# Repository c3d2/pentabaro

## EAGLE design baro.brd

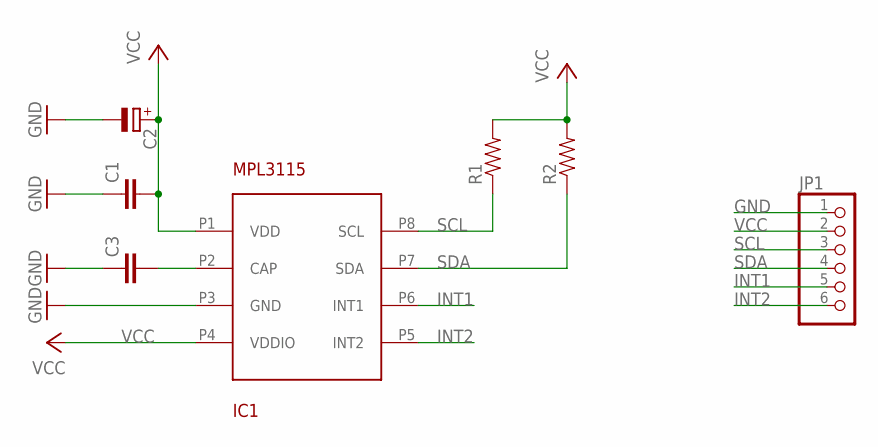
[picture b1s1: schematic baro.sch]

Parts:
C1, C3: CAP0805; 0805
C2: CPOL-EUSMCC; SMC_C
IC1: MPL3115A2; LGA8
JP1: PINHD-1X6; 1X06
R1, R2: RESISTOR0805-RES; 0805

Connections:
GND: C1.1, C2.-, C3.1, IC1.P3 (GND), JP1.1
INT1: IC1.P6 (INT1), JP1.5
INT2: IC1.P5 (INT2), JP1.6
unnamed: C3.2, IC1.P2 (CAP)
SCL: IC1.P8 (SCL), JP1.3, R1.1
SDA: IC1.P7 (SDA), JP1.4, R2.1
VCC: C1.2, C2.+, IC1.P1 (VDD), IC1.P4 (VDDIO), JP1.2, R1.2, R2.2

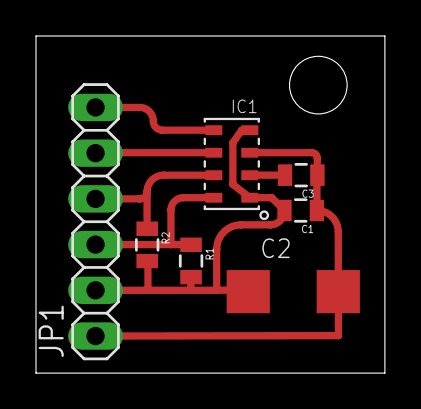
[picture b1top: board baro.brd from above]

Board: 2 copper layers, 19.4 x 18.7 mm, 7 parts (0 on the bottom side), 7 nets.

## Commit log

2012-10-06 changed sebs board proposal for module use
    one can now cut it to get an directly solderable version
2012-10-06 minor mods
2012-10-08 rundung wegen hf abstrahlung.... und weils geht

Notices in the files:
parts and their libraries:
SparkFun-Passives: Licensing: CC v3.0 Share-Alike You are welcome to use this library for commercial purposes.
